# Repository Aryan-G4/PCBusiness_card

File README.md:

# PCBusiness card: small compact nRF52 based media storage, bluetooth trancieve and macropad in a business card form factor

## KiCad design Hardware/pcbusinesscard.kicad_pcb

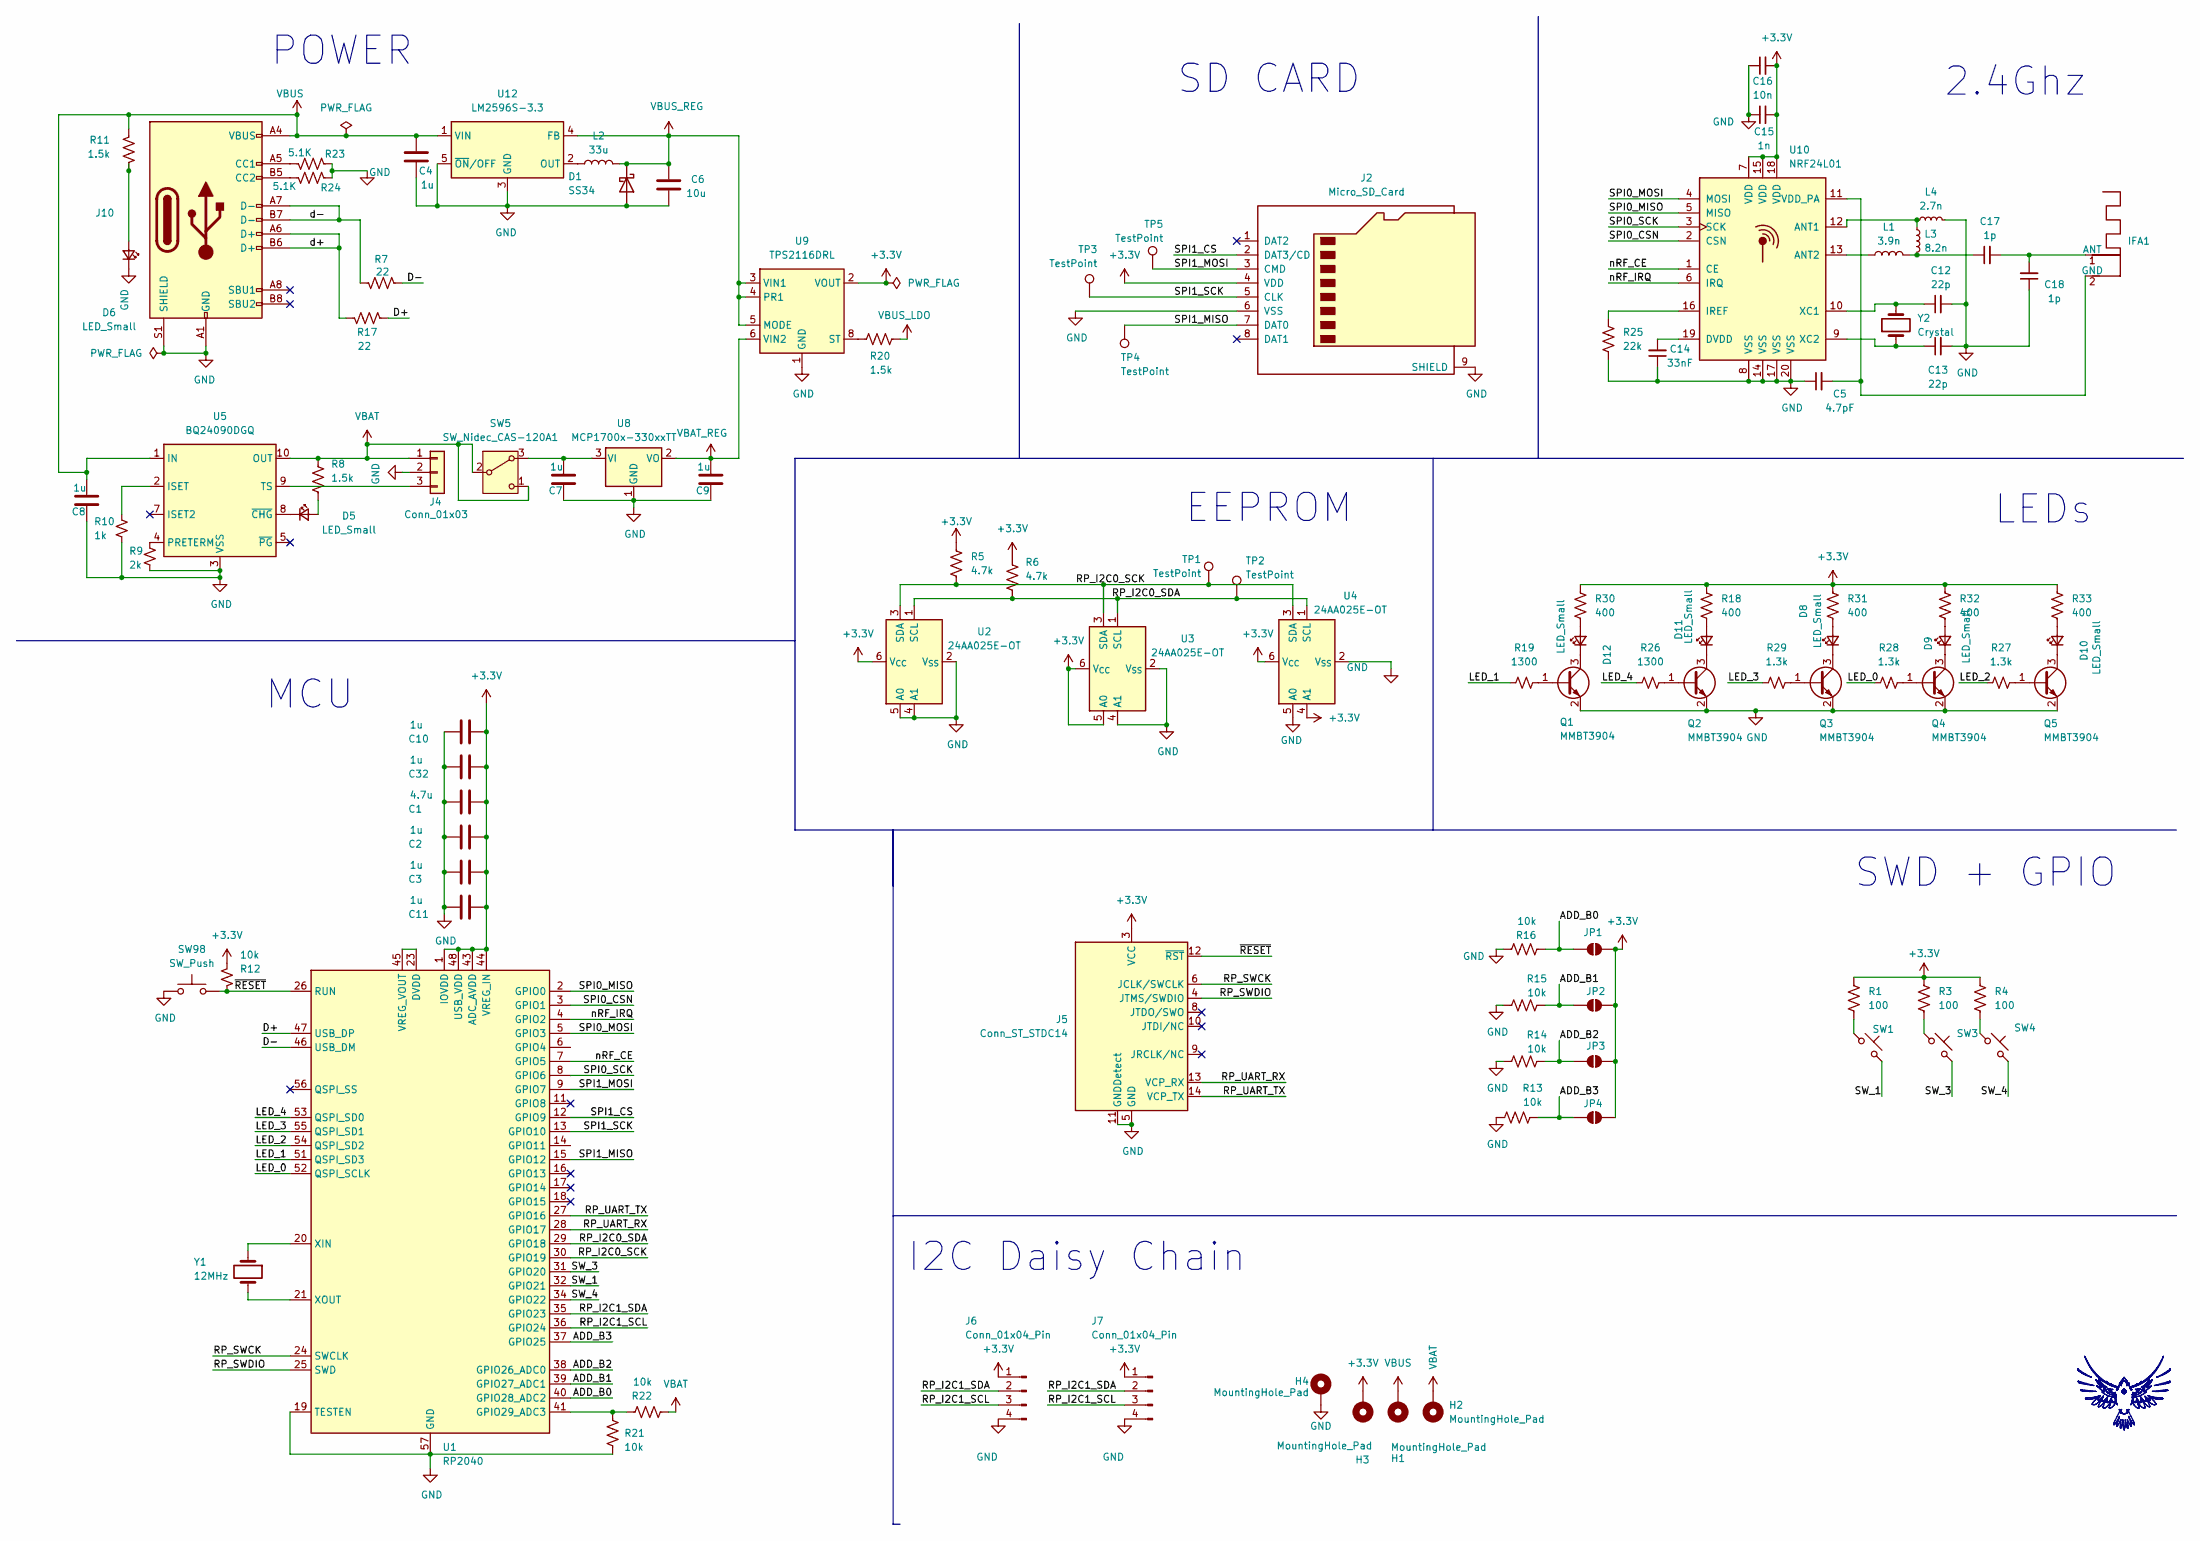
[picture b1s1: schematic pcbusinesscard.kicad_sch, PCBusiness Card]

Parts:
C1: 4.7u; C_0603_1608Metric; LCSC C14858
C2, C3, C4, C10, C11, C32: 1u; C_0603_1608Metric; LCSC C14858
C5: 4.7pF; C_0402_1005Metric
C6: 10u; C_0603_1608Metric; LCSC C14858
C7, C8, C9: 1u; C_0603_1608Metric; LCSC C15849
C12, C13: 22p; C_0402_1005Metric
C14: 33nF; C_0402_1005Metric
C15: 1n; C_0402_1005Metric
C16: 10n; C_0402_1005Metric
C17, C18: 1p; C_0402_1005Metric
D1: SS34; D_SMA
D5, D6: LED_Small; LED_D5.0mm
D8, D9, D10, D11, D12: LED_Small; LED_0805_2012Metric
H1, H2, H3, H4: MountingHole_Pad; MountingHole_2.2mm_M2_Pad_Via
IFA1: Texas_SWRA117D_2.4GHz_Right
J2: Micro_SD_Card; microSD_HC_Molex_47219-2001; LCSC C164170
J4: Conn_01x03; JST_ZH_B3B-ZR_1x03_P1.50mm_Vertical; LCSC C514175
J5: Conn_ST_STDC14; Tag-Connect_TC2070-IDC-FP_2x07_P1.27mm_Vertical
J6, J7: Conn_01x04_Pin; JST_PH_B4B-PH-K_1x04_P2.00mm_Vertical
J10: USB_C_Receptacle_USB2.0; USB_C_Receptacle_HRO_TYPE-C-31-M-12; LCSC C165948
JP1, JP2, JP3, JP4: SolderJumper_2_Open; SolderJumper-2_P1.3mm_Open_RoundedPad1.0x1.5mm
L1: 3.9n; L_0402_1005Metric
L2: 33u; L_0402_1005Metric
L3: 8.2n; L_0402_1005Metric
L4: 2.7n; L_0402_1005Metric
Q1, Q2, Q3, Q4, Q5: MMBT3904; SOT-23
R1, R3, R4: 100; R_0402_1005Metric
R5, R6: 4.7k; R_0603_1608Metric
R7, R17: 22; R_0603_1608Metric; LCSC C23186
R8, R11, R20: 1.5k; R_0603_1608Metric
R9: 2k; R_0603_1608Metric
R10: 1k; R_0603_1608Metric
R12: 10k; R_0603_1608Metric; LCSC C25804
R13, R14, R15, R16, R21, R22: 10k; R_0603_1608Metric
R18, R30, R31, R32, R33: 400; R_0402_1005Metric
R19, R26: 1300; R_0402_1005Metric
R23, R24: 5.1K; R_0603_1608Metric; LCSC C23186
R25: 22k; R_0603_1608Metric
R27, R28, R29: 1.3k; R_0402_1005Metric
SW1: ESC; MX_PCB_1.00u; LCSC C41430893
SW3: 1; MX_PCB_1.00u; LCSC C41430893
SW4: 2; MX_PCB_1.00u; LCSC C41430893
SW5: SW_Nidec_CAS-120A1; Nidec_Copal_CAS-120A
SW98: SW_Push; SW_DIP_SPSTx01_Slide_6.7x4.1mm_W6.73mm_P2.54mm_LowProfile_J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; LCSC C720477
TP1, TP2, TP3, TP4, TP5: TestPoint; TestPoint_Keystone_5010-5014_Multipurpose
U1: RP2040; QFN-56-1EP_7x7mm_P0.4mm_EP3.2x3.2mm
U2, U3, U4: 24AA025E-OT; SOT-23-6
U5: BQ24090DGQ; HVSSOP-10-1EP_3x3mm_P0.5mm_EP1.57x1.88mm_ThermalVias
U8: MCP1700x-330xxTT; SOT-23
U9: TPS2116DRL; SOT-583-8
U10: NRF24L01; QFN-20-1EP_4x4mm_P0.5mm_EP2.5x2.5mm
U12: LM2596S-3.3; TO-263-5_TabPin3
Y1: 12MHz; Crystal_SMD_5032-2Pin_5.0x3.2mm
Y2: Crystal; Crystal_SMD_HC49-SD

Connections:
+3.3V: C1.2, C2.2, C3.2, C10.2, C11.2, C15.2, C16.2, C32.2, H3.1, J2.4 (VDD), J5.3 (VCC), J6.1, J7.1, JP1.2 (B), JP2.2 (B), JP3.2 (B), JP4.2 (B), R1.1, R3.1, R4.1, R5.1, R6.1, R12.1, R18.1, R30.1, R31.1, R32.1, R33.1, U1.1 (IOVDD), U1.10 (IOVDD), U1.22 (IOVDD), U1.33 (IOVDD), U1.42 (IOVDD), U1.43 (ADC_AVDD), U1.44 (VREG_IN), U1.48 (USB_VDD), U1.49 (IOVDD), U2.6 (V_{CC}), U3.5 (A0), U3.6 (V_{CC}), U4.4 (A1), U4.6 (V_{CC}), U9.2 (VOUT), U9.7 (VOUT), U10.7 (VDD), U10.15 (VDD), U10.18 (VDD)
/ADD_B0: JP1.1 (A), R16.1, U1.40 (GPIO28_ADC2)
/ADD_B1: JP2.1 (A), R15.1, U1.39 (GPIO27_ADC1)
/ADD_B2: JP3.1 (A), R14.1, U1.38 (GPIO26_ADC0)
/ADD_B3: JP4.1 (A), R13.1, U1.37 (GPIO25)
/D+: R17.1, U1.47 (USB_DP)
/D-: R7.1, U1.46 (USB_DM)
/LED_0: R28.1, U1.52 (QSPI_SCLK)
/LED_1: R19.1, U1.51 (QSPI_SD3)
/LED_2: R27.1, U1.54 (QSPI_SD2)
/LED_3: R29.1, U1.55 (QSPI_SD1)
/LED_4: R26.1, U1.53 (QSPI_SD0)
/RP_I2C0_SCK: R5.2, TP1.1, U1.30 (GPIO19), U2.3 (SDA), U3.3 (SDA), U4.3 (SDA)
/RP_I2C0_SDA: R6.2, TP2.1, U1.29 (GPIO18), U2.1 (SCL), U3.1 (SCL), U4.1 (SCL)
/RP_I2C1_SCL: J6.3, J7.3, U1.36 (GPIO24)
/RP_I2C1_SDA: J6.2, J7.2, U1.35 (GPIO23)
/RP_SWCK: J5.6 (JCLK/SWCLK), U1.24 (SWCLK)
/RP_SWDIO: J5.4 (JTMS/SWDIO), U1.25 (SWD)
/RP_UART_RX: J5.13 (VCP_RX), U1.28 (GPIO17)
/RP_UART_TX: J5.14 (VCP_TX), U1.27 (GPIO16)
/SPI0_CSN: U1.3 (GPIO1), U10.2 (CSN)
/SPI0_MISO: U1.2 (GPIO0), U10.5 (MISO)
/SPI0_MOSI: U1.5 (GPIO3), U10.4 (MOSI)
/SPI0_SCK: U1.8 (GPIO6), U10.3 (SCK)
/SPI1_CS: J2.2 (DAT3/CD), U1.12 (GPIO9)
/SPI1_MISO: J2.7 (DAT0), TP4.1, U1.15 (GPIO12)
/SPI1_MOSI: J2.3 (CMD), TP5.1, U1.9 (GPIO7)
/SPI1_SCK: J2.5 (CLK), TP3.1, U1.13 (GPIO10)
/SW_1: SW1.2, U1.32 (GPIO21)
/SW_3: SW3.2, U1.31 (GPIO20)
/SW_4: SW4.2, U1.34 (GPIO22)
/d+: J10.A6 (D+), J10.B6 (D+), R17.2
/d-: J10.A7 (D-), J10.B7 (D-), R7.2
/nRF_CE: U1.7 (GPIO5), U10.1 (CE)
/nRF_IRQ: U1.4 (GPIO2), U10.6 (IRQ)
/~RESET: J5.12 (~RST), R12.2, SW98.1, U1.26 (RUN)
GND: C1.1, C2.1, C3.1, C4.1, C5.1, C6.1, C7.2, C8.2, C9.2, C10.1, C11.1, C12.2, C13.2, C14.1, C15.1, C16.1, C18.1, C32.1, D1.2 (A), D6.1 (K), H4.1, J2.6 (VSS), J2.9 (SHIELD), J4.2, J5.5 (GND), J5.7 (GND), J5.11 (GNDDetect), J6.4, J7.4, J10.A1 (GND), J10.A12 (GND), J10.B1 (GND), J10.B12 (GND), J10.S1 (SHIELD), L4.2, Q1.2 (E), Q2.2 (E), Q3.2 (E), Q4.2 (E), Q5.2 (E), R9.2, R10.2, R13.2, R14.2, R15.2, R16.2, R21.2, R23.1, R24.1, R25.2, SW98.2, U1.19 (TESTEN), U1.57 (GND), U2.2 (V_{SS}), U2.4 (A1), U2.5 (A0), U3.2 (V_{SS}), U3.4 (A1), U4.2 (V_{SS}), U4.5 (A0), U5.3 (VSS), U5.11 (VSS), U8.1 (GND), U9.1 (GND), U10.8 (VSS), U10.14 (VSS), U10.17 (VSS), U10.20 (VSS), U12.3 (GND), U12.5 (~ON/OFF)
unnamed: C17.1, L1.2, L3.2
unnamed: D5.2 (A), R8.2
unnamed: D5.1 (K), U5.8 (~CHG)
unnamed: D6.2 (A), R11.2
unnamed: D8.2 (A), R31.2
unnamed: D8.1 (K), Q3.3 (C)
unnamed: D9.2 (A), R32.2
unnamed: D9.1 (K), Q4.3 (C)
unnamed: D10.2 (A), R33.2
unnamed: D10.1 (K), Q5.3 (C)
unnamed: D11.2 (A), R18.2
unnamed: D11.1 (K), Q2.3 (C)
unnamed: D12.2 (A), R30.2
unnamed: D12.1 (K), Q1.3 (C)
unnamed: C17.2, C18.2, IFA1.1 (ANT)
unnamed: C5.2, IFA1.2 (GND), U10.11 (VDD_PA)
unnamed: J4.3, U5.9 (TS)
unnamed: J10.A5 (CC1), R23.2
unnamed: J10.B5 (CC2), R24.2
unnamed: Q1.1 (B), R19.2
unnamed: Q2.1 (B), R26.2
unnamed: Q3.1 (B), R29.2
unnamed: Q4.1 (B), R28.2
unnamed: Q5.1 (B), R27.2
unnamed: R1.2, SW1.1
unnamed: R3.2, SW3.1
unnamed: R4.2, SW4.1
unnamed: C7.1, SW5.3 (A), U8.3 (VI)
unnamed: R21.1, R22.1, U1.41 (GPIO29_ADC3)
unnamed: U1.23 (DVDD), U1.45 (VREG_VOUT), U1.50 (DVDD)
unnamed: U1.20 (XIN), Y1.1
unnamed: U1.21 (XOUT), Y1.2
unnamed: R10.1, U5.2 (ISET)
unnamed: R9.1, U5.4 (PRETERM)
unnamed: R20.2, U9.8 (ST)
unnamed: L3.1, L4.1, U10.12 (ANT1)
unnamed: L1.1, U10.13 (ANT2)
unnamed: C14.2, U10.19 (DVDD)
unnamed: R25.1, U10.16 (IREF)
unnamed: C12.1, U10.10 (XC1), Y2.2
unnamed: C13.1, U10.9 (XC2), Y2.1
unnamed: L2.2, U12.2 (OUT)
VBAT: H2.1, J4.1, R8.1, R22.2, SW5.1 (C), SW5.2 (B), U5.10 (OUT)
VBAT_REG: C9.1, U8.2 (VO), U9.6 (VIN2)
VBUS: C4.2, C8.1, H1.1, J10.A4 (VBUS), J10.A9 (VBUS), J10.B4 (VBUS), J10.B9 (VBUS), R11.1, U5.1 (IN), U12.1 (VIN)
VBUS_LDO: R20.1
VBUS_REG: C6.2, D1.1 (K), L2.1, U9.3 (VIN1), U9.4 (PR1), U9.5 (MODE), U12.4 (FB)

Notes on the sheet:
EEPROM
POWER
SWD + GPIO
2.4Ghz
I2C Daisy Chain
LEDs
MCU
SD CARD

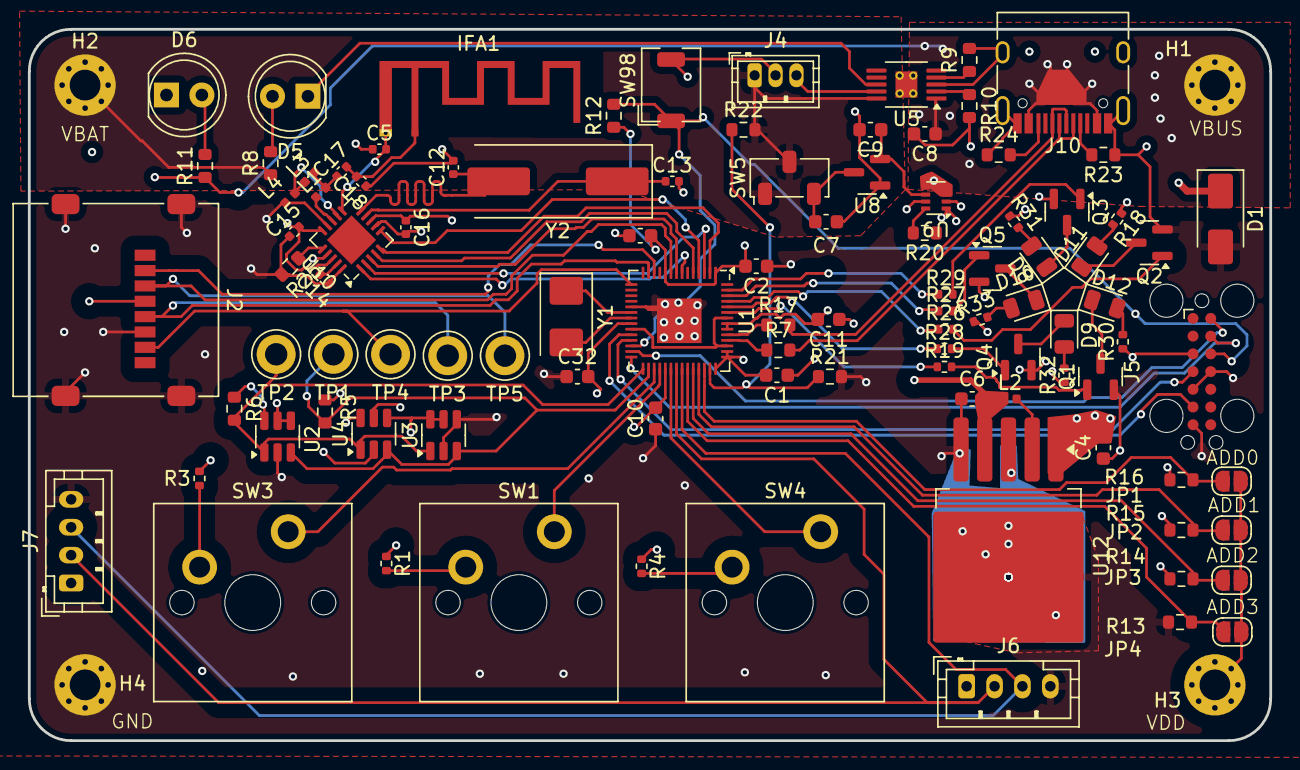
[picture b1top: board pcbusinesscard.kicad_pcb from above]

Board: 4 copper layers, 89.0 x 51.0 mm, 104 parts (0 on the bottom side), 83 nets.

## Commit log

2025-11-04 Add project description to README.md
2025-11-04 Initial commit (finished draft schematic)
2025-11-05 Overhaul entire design with RP2040
2025-11-07 adding to layout
2025-11-08 Finish Draft
2025-11-16 Finish first draft of routing
2026-02-07 dont remember
2026-02-20 Fixed DRC and cleaned up schematic
